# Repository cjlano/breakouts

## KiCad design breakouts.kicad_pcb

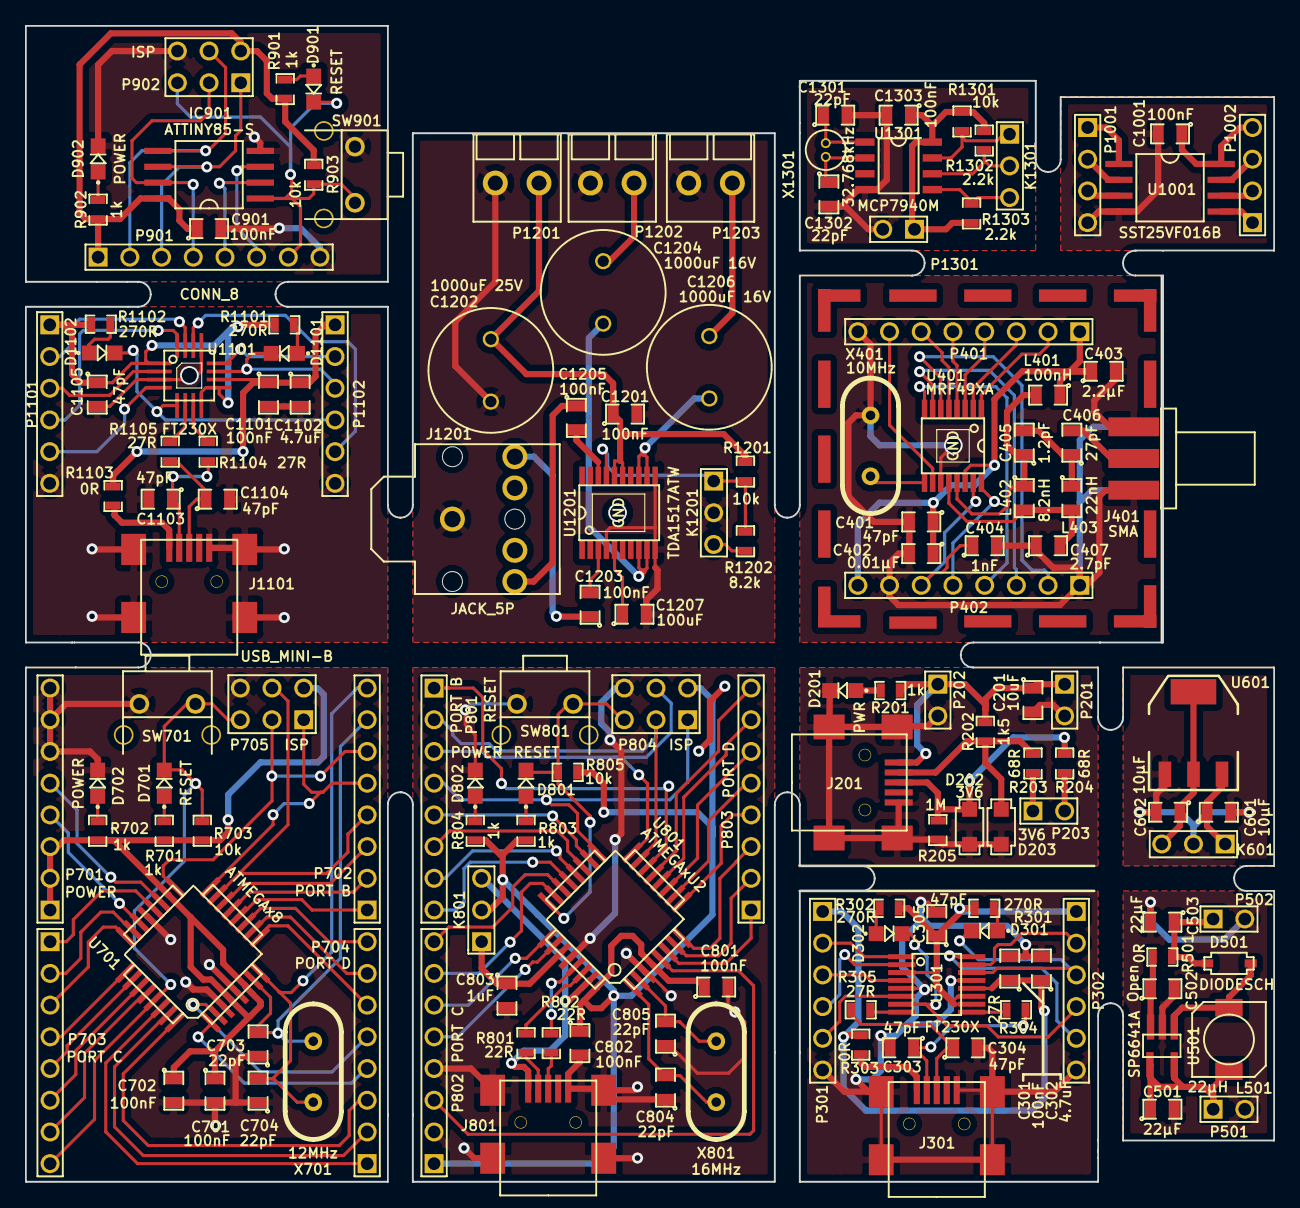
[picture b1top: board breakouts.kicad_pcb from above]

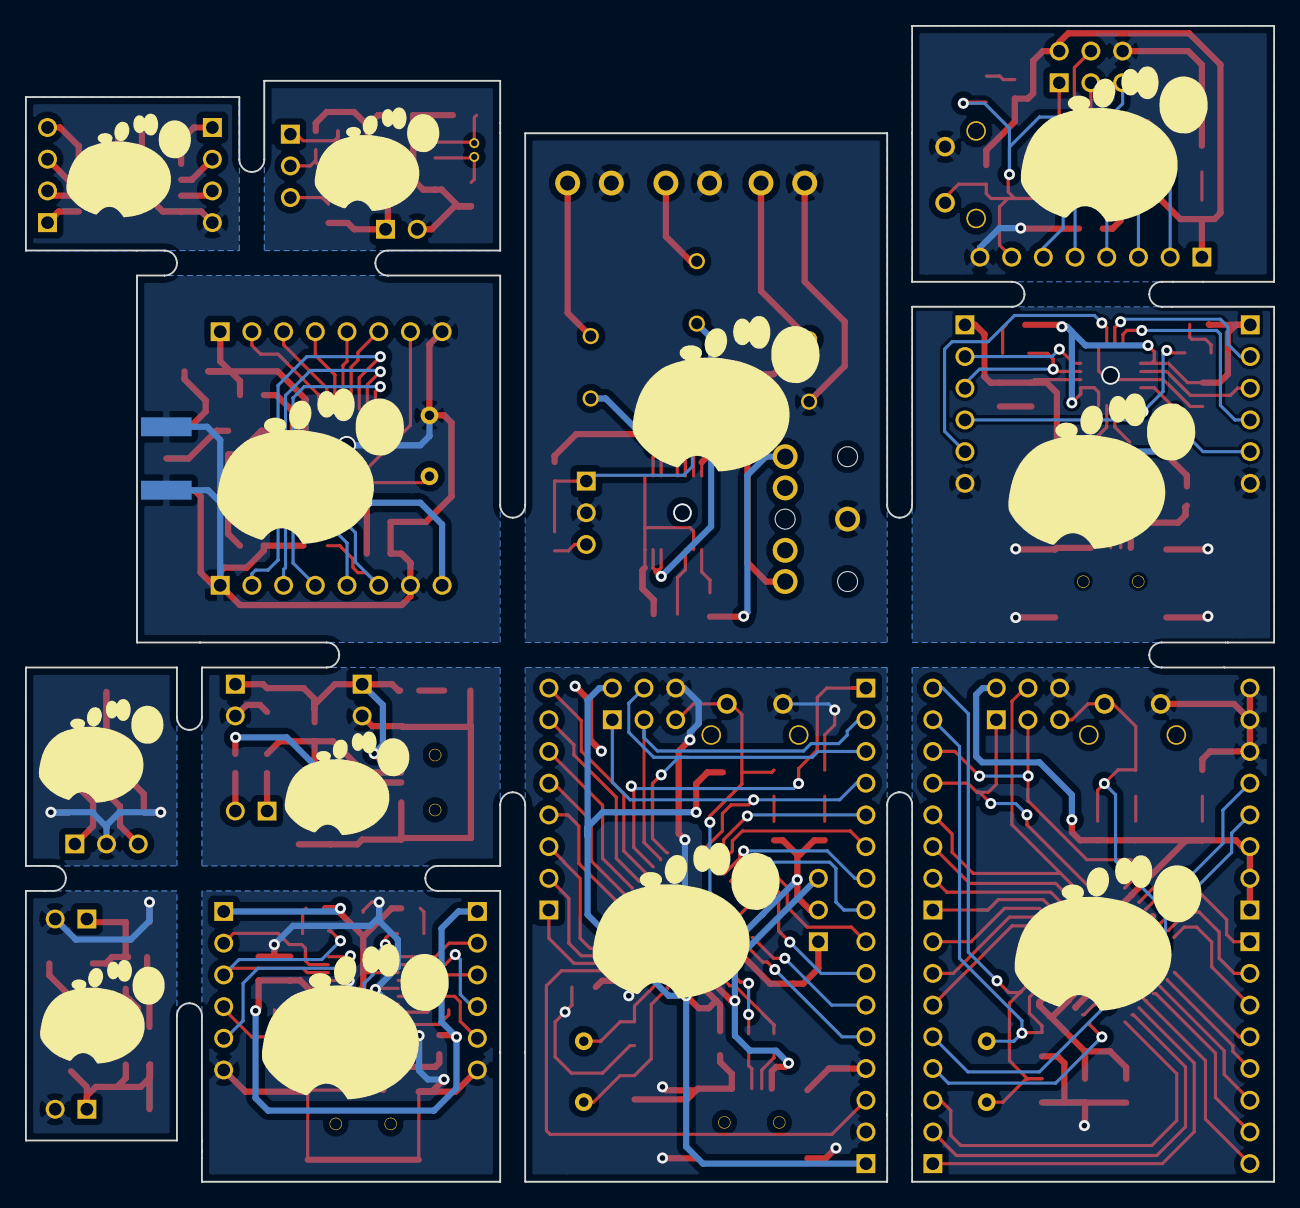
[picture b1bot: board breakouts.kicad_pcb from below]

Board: 2 copper layers, 100.0 x 92.6 mm, 165 parts (12 on the bottom side), 171 nets.

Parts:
BMIS-203_Shield: VAL**; BMIS-203_Shield
C201: 10uF; SMD0805
C301, C701, C702, C801, C802, C901, C1001, C1101, C1201, C1203, C1205, C1303: 100nF; SMD0805
C302, C1102: 4.7uF; SMD0805
C303, C304, C305, C401, C1103, C1104, C1105: 47pF; SMD0805
C402: 0.01µF; SMD0805
C403: 2.2µF; SMD0805
C404: 1nF; SMD0805
C405: 1.2pF; SMD0805
C406: 27pF; SMD0805
C407: 2.7pF; SMD0805
C501, C503: 22µF; SMD0805
C502: Open; SMD0805
C601, C602: 10µF; SMD0805
C703, C704, C804, C805, C1301, C1302: 22pF; SMD0805
C803: 1uF; SMD0805
C1202: 1000uF 25V; C_radial_10mm
C1204, C1206: 1000uF 16V; C_radial_10mm
C1207: 100uF; SMD0805
D201: PWR; LED-0805
D202, D203: 3V6; SOD123F
D301, D302, D1101, D1102: LED; LED-0805
D501: DIODESCH; SOD-123
D701, D801, D901: RESET; LED-0805
D702, D802, D902: POWER; LED-0805
G*: footprint; footprint-10
G*#2, G*#3, G*#4, G*#5, G*#6, G*#7, G*#8: footprint; footprint-15
G*#9, G*#10, G*#11, G*#12: footprint; footprint-10
IC901: ATTINY85-S; SOIC-8
J201, J301, J801, J1101: USB_MINI-B; mini-USB
J401: SMA; PCBedge_SMA
J1201: JACK_5P; JACK_3.5mm
K601, K801, K1201, K1301: CONN_3; pin_array_3x1
L401: 100nH; SMD0805
L402: 8.2nH; SMD0805
L403: 22nH; SMD0805
L501: 22µH; Shielded_inductor
P201, P202, P203, P501, P502, P1301: CONN_2; pin_array_2x1
P301, P302, P1101, P1102: CONN_6; pin_array_6x1
P401, P402, P901: CONN_8; pin_array_8x1
P701: POWER; pin_array_8x1
P702, P801: PORT B; pin_array_8x1
P703, P802: PORT C; pin_array_8x1
P704, P803: PORT D; pin_array_8x1
P705, P804, P902: ISP; pin_array_3x2
P1001, P1002: CONN_4; pin_array_4x1
P1201, P1202, P1203: CONN_2; Screw_Terminal_Block_2P
R201, R701, R702, R803, R804, R901, R902: 1k; SMD0603
R202: 1k5; SMD0603
R203, R204: 68R; SMD0603
R205: 1M; SMD0603
R301, R302, R1101, R1102: 270R; SMD0603
R303, R501, R1103: 0R; SMD0603
R304, R305, R1104, R1105: 27R; SMD0603
R703, R805, R903, R1201, R1301: 10k; SMD0603
R801, R802: 22R; SMD0603
R1202: 8.2k; SMD0603
R1302, R1303: 2.2k; SMD0603
SW701, SW901: SW_PUSH; PUSH_BUTTON-TECon
SW801: RESET; PUSH_BUTTON-TECon
U301: FT230X; SSOP-16
U401: MRF49XA; TSSOP-16
U501: SP6641A; SOT-23
U601: NX1117C33Z; SOT223
U701: ATMEGAx8; TQFP32-0.8mm
U801: ATMEGAxU2; TQFP32-0.8mm
U1001: SST25VF016B; SOIC-8
U1101: FT230X; QFN-16
U1201: TDA1517ATW; TSSOP-20
U1301: MCP7940M; SOIC-8_Narrow_3.90mm
X401: 10MHz; HC49US
X701: 12MHz; HC49US
X801: 16MHz; HC49US
X1301: 32.768kHz; AB38T_Crystal
slot-10mm, slot-10mm#2: VAL**; slot-10mm

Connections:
/AVR-ATmegax8/ADC6: P701.5, U701.19
/AVR-ATmegax8/ADC7: P701.4, U701.22
/AVR-ATmegax8/AREF: P703.1, U701.20
/AVR-ATmegax8/MISO: P702.5, P705.1, U701.16
/AVR-ATmegax8/MOSI: P702.4, P705.4, U701.15
/AVR-ATmegax8/PB0: P702.1, U701.12
/AVR-ATmegax8/PB1: P702.2, U701.13
/AVR-ATmegax8/PB2: P702.3, U701.14
/AVR-ATmegax8/PB5: P702.6, P705.3, U701.17
/AVR-ATmegax8/PB6: C703.2, P702.7, U701.7, X701.2
/AVR-ATmegax8/PB7: C704.2, P702.8, U701.8, X701.1
/AVR-ATmegax8/PC0: P703.2, U701.23
/AVR-ATmegax8/PC1: P703.3, U701.24
/AVR-ATmegax8/PC2: P703.4, U701.25
/AVR-ATmegax8/PC3: P703.5, U701.26
/AVR-ATmegax8/PC4: P703.6, U701.27
/AVR-ATmegax8/PC5: P703.7, U701.28
/AVR-ATmegax8/PC6: D701.2, P703.8, P705.5, R703.2, SW701.1, U701.29
/AVR-ATmegax8/PD0: P704.1, U701.30
/AVR-ATmegax8/PD1: P704.2, U701.31
/AVR-ATmegax8/PD2: P704.3, U701.32
/AVR-ATmegax8/PD3: P704.4, U701.1
/AVR-ATmegax8/PD4: P704.5, U701.2
/AVR-ATmegax8/PD5: P704.6, U701.9
/AVR-ATmegax8/PD6: P704.7, U701.10
/AVR-ATmegax8/PD7: P704.8, U701.11
/AVR-ATmegaxU2/AVR_VCC: C801.1, C802.1, K801.2, P802.1, P804.2, R803.1, R804.1, R805.1, U801.4, U801.32
/AVR-ATmegaxU2/MISO: P801.4, P804.1, U801.17
/AVR-ATmegaxU2/MOSI: P801.3, P804.4, U801.16
/AVR-ATmegaxU2/PB0: P801.1, U801.14
/AVR-ATmegaxU2/PB1: P801.2, P804.3, U801.15
/AVR-ATmegaxU2/PB4: P801.5, U801.18
/AVR-ATmegaxU2/PB5: P801.6, U801.19
/AVR-ATmegaxU2/PB6: P801.7, U801.20
/AVR-ATmegaxU2/PB7: P801.8, U801.21
/AVR-ATmegaxU2/PC2: P802.3, U801.5
/AVR-ATmegaxU2/PC4: P802.5, U801.26
/AVR-ATmegaxU2/PC5: P802.6, U801.25
/AVR-ATmegaxU2/PC6: P802.7, U801.23
/AVR-ATmegaxU2/PC7: P802.8, U801.22
/AVR-ATmegaxU2/PD0: P803.1, U801.6
/AVR-ATmegaxU2/PD1: P803.2, U801.7
/AVR-ATmegaxU2/PD2: P803.3, U801.8
/AVR-ATmegaxU2/PD3: P803.4, U801.9
/AVR-ATmegaxU2/PD4: P803.5, U801.10
/AVR-ATmegaxU2/PD5: P803.6, U801.11
/AVR-ATmegaxU2/PD6: P803.7, U801.12
/AVR-ATmegaxU2/PD7: P803.8, U801.13
/AVR-ATmegaxU2/UCAP: C803.1, K801.1, U801.27
/AVR-ATmegaxU2/XTAL1: C804.2, U801.1, X801.2
/AVR-ATmegaxU2/XTAL2: C805.2, U801.2, X801.1
/AVR-ATmegaxU2/~RESET: D801.2, P804.5, R805.2, SW801.1, U801.24
/AVR-ATtinyx5/MISO: IC901.6, P901.3, P902.1
/AVR-ATtinyx5/MOSI: IC901.5, P901.2, P902.4
/AVR-ATtinyx5/PB2: IC901.7, P901.4, P902.3
/AVR-ATtinyx5/PB3: IC901.2, P901.5
/AVR-ATtinyx5/PB4: IC901.3, P901.6
/AVR-ATtinyx5/PB5: D901.2, IC901.1, P901.7, P902.5, R903.2, SW901.1
/Audio amplifier/Mute: K1201.3, R1202.2
/Audio amplifier/StandBy: K1201.1, R1201.2, R1202.1, U1201.17
/FT230X-QFN/CBUS0: P1102.2, U1101.12
/FT230X-QFN/CBUS1: D1101.2, P1102.3, U1101.11
/FT230X-QFN/CBUS2: D1102.2, P1102.4, U1101.5
/FT230X-QFN/CBUS3: P1102.5, U1101.14
/FT230X-QFN/RxD: P1101.3, U1101.2
/FT230X-QFN/TxD: P1101.2, U1101.15
/FT230X-QFN/VCCIO: C1105.1, P1101.1, R1101.1, R1102.1, U1101.1, U1101.8, U1101.9
/FT230X-QFN/~CTS: P1101.5, U1101.4
/FT230X-QFN/~RTS: P1101.4, U1101.16
/FT230X/CBUS0: P302.2, U301.15
/FT230X/CBUS1: D301.2, P302.3, U301.14
/FT230X/CBUS2: D302.2, P302.4, U301.7
/FT230X/CBUS3: P302.5, U301.16
/FT230X/RxD: P301.3, U301.4
/FT230X/TxD: P301.2, U301.1
/FT230X/VCCIO: C305.1, P302.1, R301.1, R302.1, U301.3, U301.10, U301.11
/FT230X/~CTS: P301.5, U301.6
/FT230X/~RTS: P301.4, U301.2
/MRF49XA/Radio_CLKOUT: P402.4, U401.8
/MRF49XA/Radio_DIO: P402.5, U401.16
/MRF49XA/Radio_FINT: P402.3, U401.7
/MRF49XA/Radio_RSSIO: C404.1, P402.6, U401.15
/MRF49XA/Radio_SPI_CLK: P401.3, U401.2
/MRF49XA/Radio_SPI_MISO: P401.5, U401.4
/MRF49XA/Radio_SPI_MOSI: P401.2, U401.1
/MRF49XA/~Radio_FSEL: P402.2, U401.6
/MRF49XA/~Radio_IRO: P401.6, U401.5
/MRF49XA/~Radio_SPI_CS: P401.4, U401.3
/step-up/VBATT: C501.1, L501.1, P501.1, U501.4, U501.5
/step-up/Vout: C503.1, D501.2, P502.1, R501.2
/voltage-reg/Vin: C601.1, K601.1, U601.3
/voltage-reg/Vout: C602.1, K601.3, U601.2, U601.4
GND1: C201.2, D201.2, D202.1, D203.1, J201.5, J201.6, J201.7, J201.8, J201.9, P201.2, P202.2, R205.1
GND2: C301.2, C302.2, C303.2, C304.2, C305.2, J301.5, J301.6, J301.7, J301.8, J301.9, P301.6, P302.6, U301.5, U301.13
GND3: C1101.2, C1102.2, C1103.2, C1104.2, C1105.2, J1101.5, J1101.6, J1101.7, J1101.8, J1101.9, P1101.6, P1102.6, U1101.3, U1101.13
GND4: C501.2, C502.2, C503.2, P501.2, P502.2, U501.2
GND5: C601.2, C602.2, K601.2, U601.1
GND6: C701.2, C702.2, C703.1, C704.1, D702.2, P701.6, P701.7, P701.8, P705.6, SW701.2, U701.3, U701.5, U701.21
GND7: C801.2, C802.2, C803.2, C804.1, C805.1, D802.2, J801.5, J801.6, J801.7, J801.8, J801.9, P802.2, P802.4, P804.6, SW801.2, U801.3, U801.28
GND8: C901.2, D902.2, IC901.4, P901.8, P902.6, SW901.2
GND9: C1001.2, P1001.4, U1001.4
GND10: C401.2, C402.2, C403.2, C404.2, C407.1, J401.2, J401.3, J401.4, J401.5, P401.8, P402.1, P402.7, U401.11, X401.1
GND11: C1201.2, C1202.2, C1207.2, J1201.1, K1201.2, P1201.2, P1202.2, P1203.2, U1201.4, U1201.10, U1201.11
GND12: C1301.2, C1302.2, C1303.2, P1301.2, U1301.4
unnamed: D202.2, J201.3, R204.1, R205.2
unnamed: D203.2, J201.2, R202.1, R203.1
unnamed: P203.1, R203.2
unnamed: D201.1, R201.2
unnamed: P203.2, R204.2
unnamed: R305.1, U301.8
unnamed: R304.1, U301.9
unnamed: C303.1, J301.2, R304.2
unnamed: C304.1, J301.3, R305.2
unnamed: J301.1, R303.2
unnamed: D302.1, R302.2
unnamed: D301.1, R301.2
unnamed: C406.2, J401.1
unnamed: U401.9, X401.2
unnamed: C407.2, L402.2, L403.2, U401.12
unnamed: C405.2, C406.1, L403.1
unnamed: C405.1, L401.2, L402.1, U401.13
unnamed: D501.1, L501.2, U501.1
unnamed: C502.1, R501.1, U501.3
unnamed: D702.1, R702.2
unnamed: D701.1, R701.2
unnamed: J801.2, R801.1
unnamed: J801.1, K801.3, U801.31
unnamed: R801.2, U801.30
unnamed: R802.2, U801.29
unnamed: J801.3, R802.1
unnamed: D801.1, R803.2
unnamed: D802.1, R804.2
unnamed: D901.1, R901.2
unnamed: D902.1, R902.2
unnamed: P1002.1, U1001.5
unnamed: P1002.2, U1001.6
unnamed: P1002.3, U1001.7
unnamed: P1001.1, U1001.1
unnamed: P1001.2, U1001.2
unnamed: P1001.3, U1001.3
unnamed: R1105.1, U1101.6
unnamed: R1104.1, U1101.7
unnamed: J1101.1, R1103.2
unnamed: C1103.1, J1101.2, R1104.2
unnamed: C1104.1, J1101.3, R1105.2
unnamed: D1101.1, R1101.2
unnamed: D1102.1, R1102.2
unnamed: C1207.1, U1201.5
unnamed: C1203.2, U1201.3
unnamed: C1205.2, U1201.18
unnamed: C1203.1, J1201.2
unnamed: C1205.1, J1201.5
unnamed: C1206.1, U1201.12, U1201.13
unnamed: C1204.1, U1201.8, U1201.9
unnamed: C1204.2, P1202.1
unnamed: C1206.2, P1203.1
unnamed: C1301.1, U1301.1, X1301.2
unnamed: C1302.1, U1301.2, X1301.1
unnamed: K1301.1, R1301.2, U1301.7
unnamed: K1301.3, R1303.2, U1301.5
unnamed: K1301.2, R1302.2, U1301.6
Radio_RESETn: P401.7, U401.10
VCC1: C201.1, J201.1, P201.1, P202.1, R201.1, R202.2
VCC2: C301.1, C302.1, P301.1, R303.1, U301.12
VCC3: C1101.1, C1102.1, P1102.1, R1103.1, U1101.10
VCC6: C701.1, C702.1, P701.1, P701.2, P701.3, P705.2, R701.1, R702.1, R703.1, U701.4, U701.6, U701.18
VCC8: C901.1, IC901.8, P901.1, P902.2, R901.1, R902.1, R903.1
VCC9: C1001.1, P1002.4, U1001.8
VCC10: C401.1, C402.1, C403.1, L401.1, P401.1, P402.8, U401.14
VCC11: C1201.1, C1202.1, P1201.1, R1201.1, U1201.15, U1201.16
VCC12: C1303.1, P1301.1, R1301.1, R1302.1, R1303.1, U1301.8

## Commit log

2013-10-19 .gitignore *.bak
2013-10-19 Import Kicad project + schematics
2013-11-17 Each breakout has its own power/GND
    GND is not shared between board, neither VCC.
    This will allow a separate GND plane for each sub-board.
2013-11-17 Add title and license to schematic pages
    License: Creative Commons Attribution, Share Alike (CC-BY-SA)
2013-11-26 Add details on (big) capacitors
2013-11-26 Add new files: NetList, PCB, footprint association
2013-11-27 More module association
2013-11-28 Fix global signals
2013-11-28 Fix resistor footprint + add crystal
2013-11-28 Start PCB placing
2013-11-29 Fix VCCxx power symbols and nets
2013-12-01 Start placing component
2013-12-05 More placing
2013-12-14 more placement
2013-12-14 Component placement done
2013-12-14 Begin slot/breakaway placement
2013-12-15 breakaway placement
2013-12-22 slots and breakaways
2014-01-02 breakaway and slots placement
2014-01-02 Board edges
2014-01-02 Fix PCB edge
2014-01-02 Route AVR ATtinyx5 board
2014-01-03 Rework and route FT230X-QFN board
2014-01-04 Route ATmegax8 board
2014-01-04 Route ATmegaxU2 board
2014-01-04 Route Audio amplifier board
2014-01-04 Route FT230X board
2014-01-04 Route step-up and voltage regulator boards
2014-01-04 Route Flash and RTC boards
2014-01-04 Route MRF49XA board
2014-01-05 Place silkscreen text (ref and values)
2014-02-26 Add logos on bottom side + logo lib
2014-02-26 Gerbers: Seeedstudio submission
2014-02-26 Rework PCB edge
    Seeedstudio does not accept slots/break-away so I remove them all.
    Rework PCB edge to ease board separation.
2014-02-26 Second gerber generation: no more breakaway or slot
